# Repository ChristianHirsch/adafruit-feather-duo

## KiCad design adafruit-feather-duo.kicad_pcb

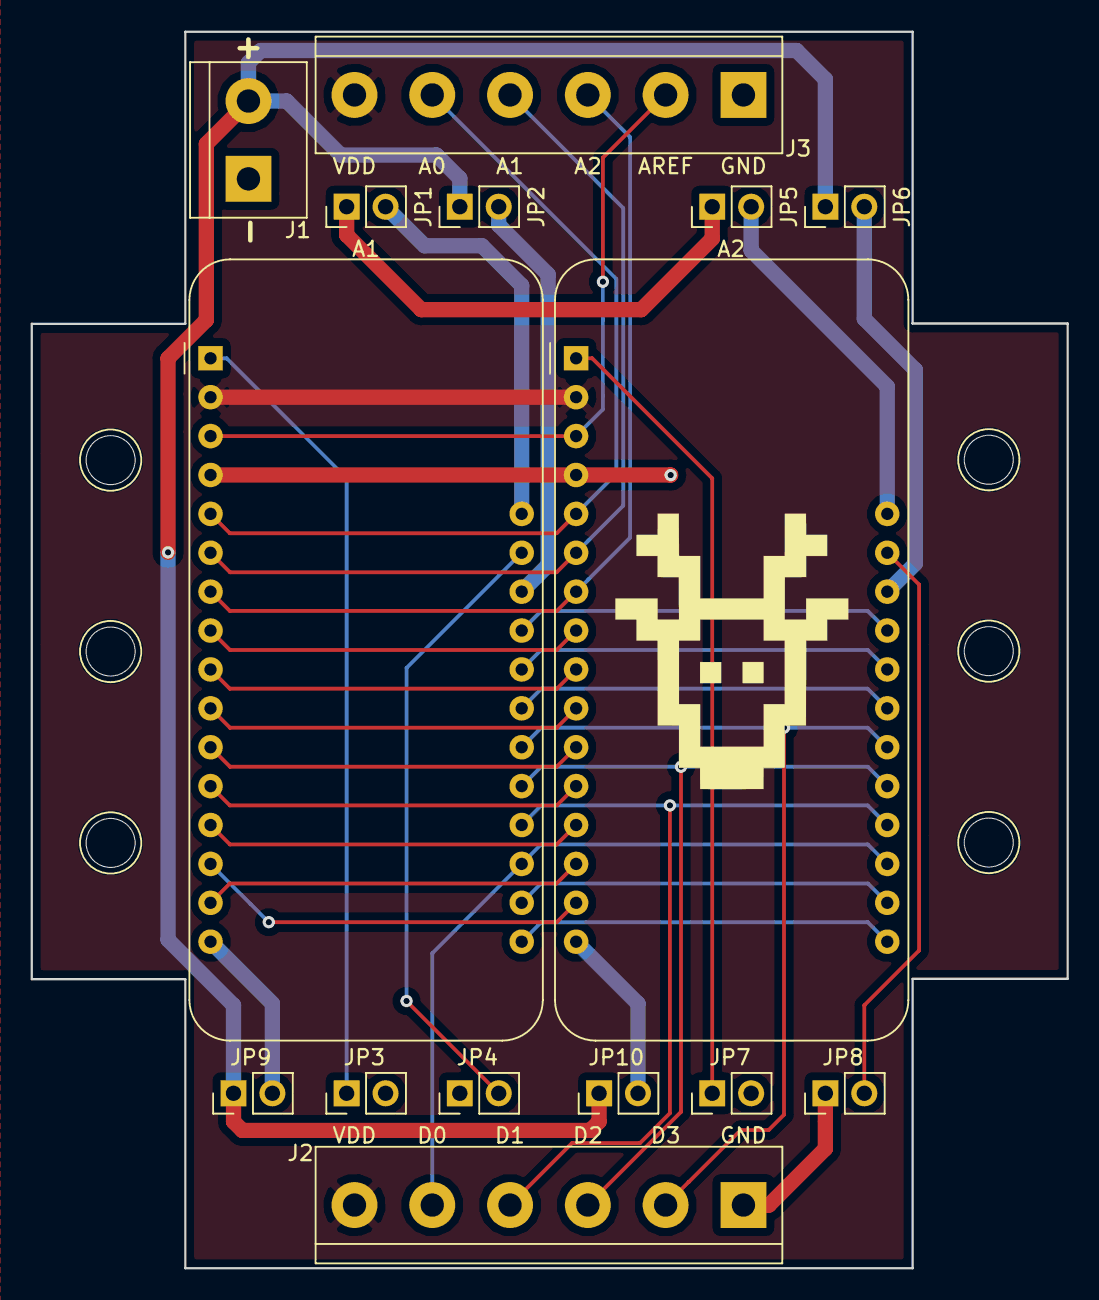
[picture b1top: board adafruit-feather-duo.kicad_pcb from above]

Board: 2 copper layers, 67.6 x 80.8 mm, 17 parts (0 on the bottom side), 35 nets.

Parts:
A1: ActiniusIcarus; Adafruit_Feather
A2: ParticleXenon; Adafruit_Feather
DRA1, DRA2: DIN_Rail_Adapter; DINRailAdapter_3xM3_PhoenixContact_1201578
J1: Solar; TerminalBlock_bornier-2_P5.08mm
J2, J3: Conn_01x06; TerminalBlock_bornier-6_P5.08mm
JP1, JP2, JP3, JP4, JP5, JP6, JP7, JP8, JP9, JP10: Jumper_2_Open; PinHeader_1x02_P2.54mm_Vertical

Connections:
+BATT: JP1.1, JP5.1
/A0: A1.5, A2.5, J3.5
/A1: A1.6, A2.6, J3.4
/A2: A1.7, A2.7, J3.3
/A3: A1.8, A2.8
/A4: A1.9, A2.9
/A5: A1.10, A2.10
/AREF: A1.3, A2.3, J3.2
/D0: A1.19, A2.19, J2.2
/D1: A1.20, A2.20, J2.3
/D2: A1.21, A2.21, J2.4
/D3: A1.22, A2.22, J2.5
/D4: A1.23, A2.23
/D5: A1.24, A2.24
/D6: A1.25, A2.25
/I2C_SCL: A1.18, A2.18
/I2C_SDA: A1.17, A2.17
/SERIAL_RX: A1.14, A2.15
/SERIAL_TX: A1.15, A2.14
/SPI_MISO: A1.12, A2.12
/SPI_MOSI: A1.13, A2.13
/SPI_SCK: A1.11, A2.11
/V_USB: J1.1, JP2.1, JP6.1, JP9.1, JP10.1
GNDD: A1.4, A2.4, J1.2, J2.6, J3.1, JP4.1, JP8.1
unnamed: A1.1, JP3.1
unnamed: A1.16, JP9.2
unnamed: A1.26, JP2.2
unnamed: A1.27, JP4.2
unnamed: A1.28, JP1.2
unnamed: A2.1, JP7.1
unnamed: A2.16, JP10.2
unnamed: A2.26, JP6.2
unnamed: A2.27, JP8.2
unnamed: A2.28, JP5.2
VDD: A1.2, A2.2, J2.1, J3.6
